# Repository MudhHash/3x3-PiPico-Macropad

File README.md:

# 9x9-PiPico-Keypad
This 9-key macropad is designed using a Raspberry Pi Pico microcontroller programmed with CircuitPython using KMK firmware.

## Overview
This repository provides the schematics and code used in this project. The goal of this project was to build a compact, low-cost, and easily programmable marcopad which ultimately serve the purpose of offering quick access to frequently used shortcuts, macros, and commands in a streamlined, tactile form.

## Bill of Materials

Item | Quantity | Cost
--- | --- | ---
Macropad PCB | 1 | $0.40 (Excluding Shipping)
Raspberry Pi Pico | 1 | $9.95 
Mechanical Keyboard Switch | 10 | $4.89
PBT Blank Keycaps | 10 | $9.59

## PCB
The PCB was designed using KiCAD with a focus on simplicity, compactness, and ease of assembly. It includes all the necessary connections for the microcontroller, switches, and diodes, while minimizing overall footprint and cost.

[Files](https://github.com/MudhHash/3x3-PiPico-Macropad/tree/main/PCB) Included:
* .kicad_pcb – Main PCB layout
* .sch – Schematic design

## Firmware and Code
This macropad uses KMK Firmware, keyboard firmware written in CircuitPython. KMK is ideal for small custom keyboards and macropads due to its ease of use, real-time reprogrammability, and active development community.

How to Implement:
* Flash the CircuitPython .uf2 file for your board from [circuitpython.org](https://circuitpython.org/downloads)
* Drag-and-drop the firmware onto the mounted USB drive (CIRCUITPY)
* Install [KMK](https://github.com/KMKfw/kmk_firmware) by copying its files into the lib directory on the device
* Add or edit the code.py file to define your keymap and macros
* Example Code:
```bash
import board  # Access pin definitions specific to the microcontroller
from kmk.kmk_keyboard import KMKKeyboard  # Base KMK keyboard class
from kmk.keys import KC  # Keycode library for standard key constants
from kmk.scanners.digitalio import DiodeOrientation  # Diode orientation options for the matrix

# Create a keyboard object instance
keyboard = KMKKeyboard()

# Define the row and column GPIO pins based on your physical wiring
keyboard.row_pins = (board.GP10, board.GP11, board.GP12)  # 3 row pins
keyboard.col_pins = (board.GP6, board.GP7, board.GP8)     # 3 column pins

# Specify the diode orientation used in the matrix (important for correct scanning)
keyboard.diode_orientation = DiodeOrientation.COL2ROW

# Define the keymap layout as a flat list of keycodes (3x3 matrix in this case)
keyboard.keymap = [
    [KC.KP_1, KC.KP_2, KC.KP_3,
     KC.KP_4, KC.KP_5, KC.KP_6,
     KC.KP_7, KC.KP_8, KC.KP_9]
]

# Run the keyboard firmware loop when the script is executed
if __name__ == '__main__':
    keyboard.go()

```

Feel free to modify the code to suit your own workflow!

## Resources
* KiCad Footprints: The component footprints used in this project were sourced from [ScottoKeebs](https://github.com/joe-scotto/scottokeebs).

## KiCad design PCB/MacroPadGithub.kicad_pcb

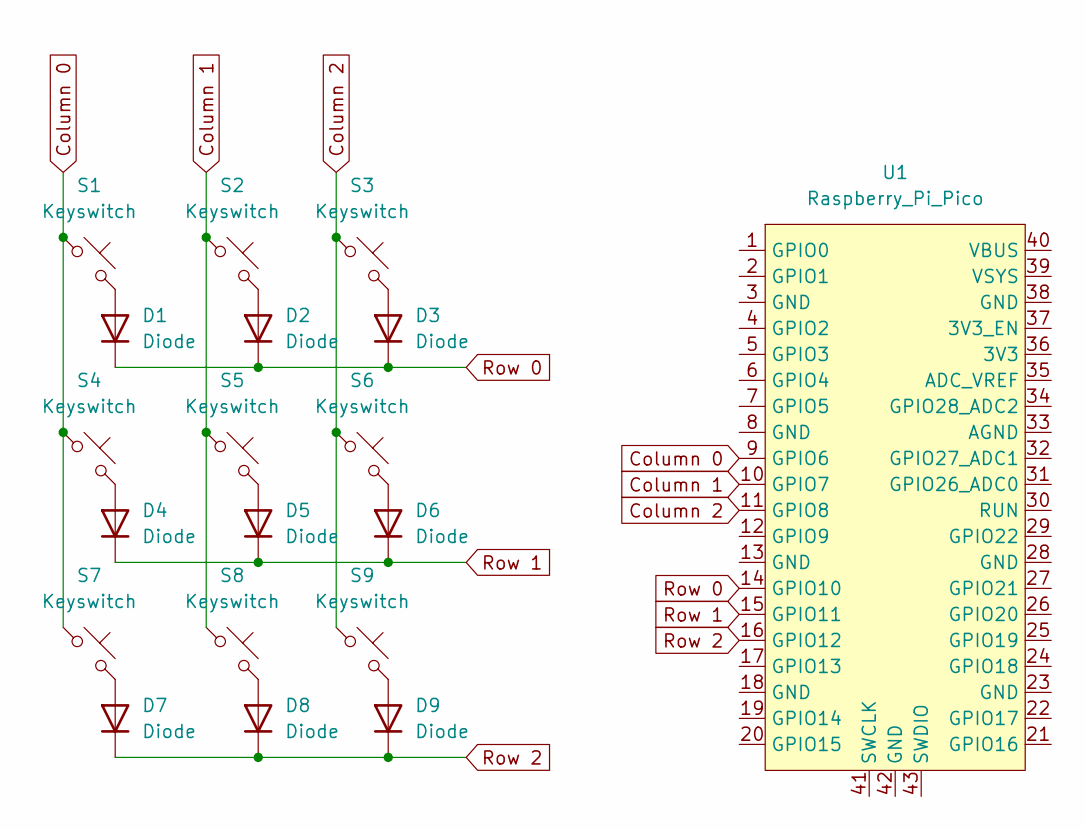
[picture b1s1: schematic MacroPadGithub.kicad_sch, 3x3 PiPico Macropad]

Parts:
D1, D2, D3, D4, D5, D6, D7, D8, D9: Diode; Diode_SOD-123
S1, S2, S3, S4, S5, S6, S7, S8, S9: Keyswitch; MX_PCB_1.00u
U1: Raspberry_Pi_Pico

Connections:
Column 0: S1.1, S4.1, S7.1, U1.9 (GPIO6)
Column 1: S2.1, S5.1, S8.1, U1.10 (GPIO7)
Column 2: S3.1, S6.1, S9.1, U1.11 (GPIO8)
unnamed: D1.2 (A), S1.2
unnamed: D2.2 (A), S2.2
unnamed: D3.2 (A), S3.2
unnamed: D4.2 (A), S4.2
unnamed: D5.2 (A), S5.2
unnamed: D6.2 (A), S6.2
unnamed: D7.2 (A), S7.2
unnamed: D8.2 (A), S8.2
unnamed: D9.2 (A), S9.2
Row 0: D1.1 (K), D2.1 (K), D3.1 (K), U1.14 (GPIO10)
Row 1: D4.1 (K), D5.1 (K), D6.1 (K), U1.15 (GPIO11)
Row 2: D7.1 (K), D8.1 (K), D9.1 (K), U1.16 (GPIO12)

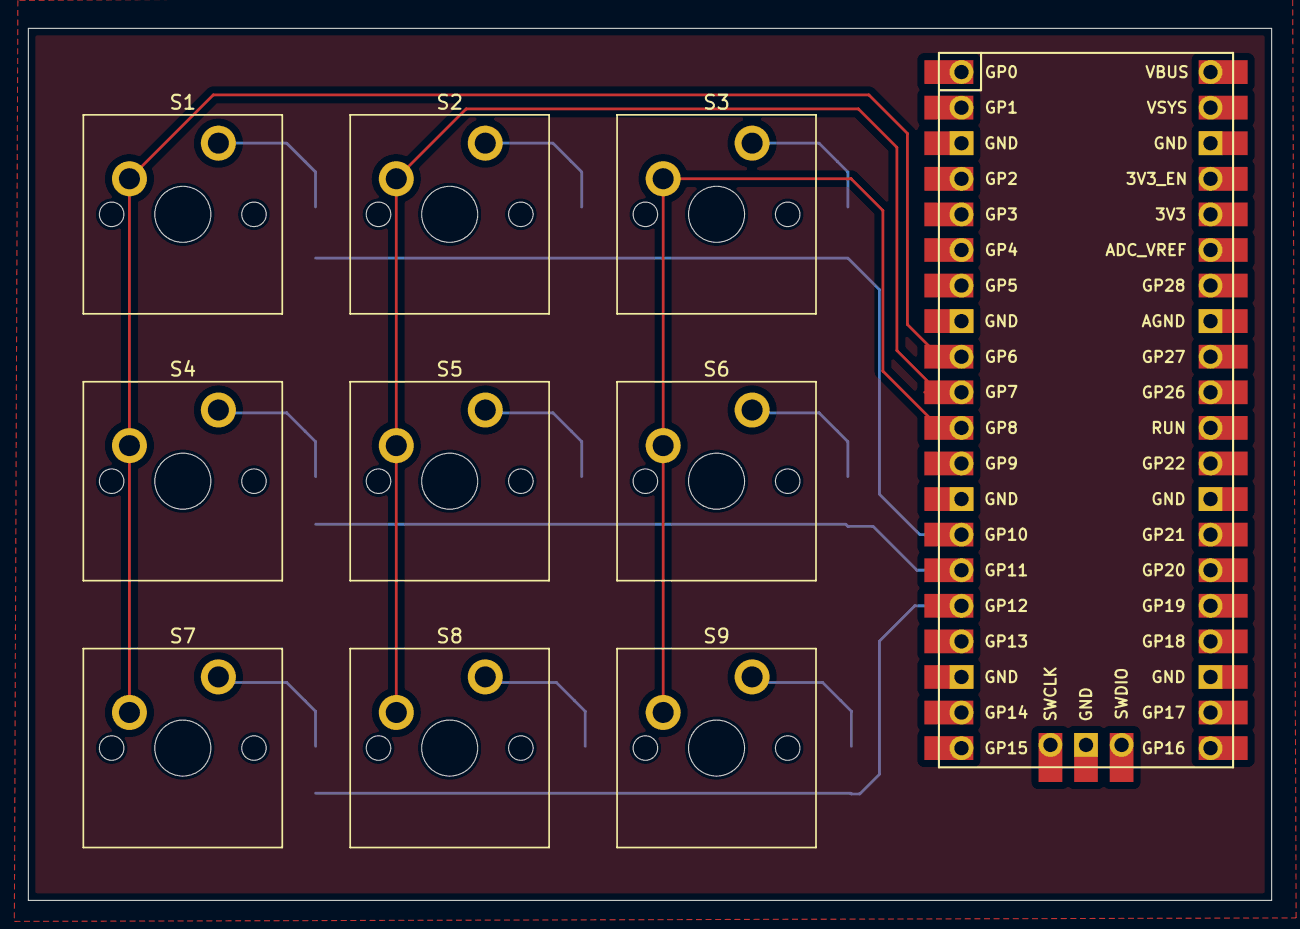
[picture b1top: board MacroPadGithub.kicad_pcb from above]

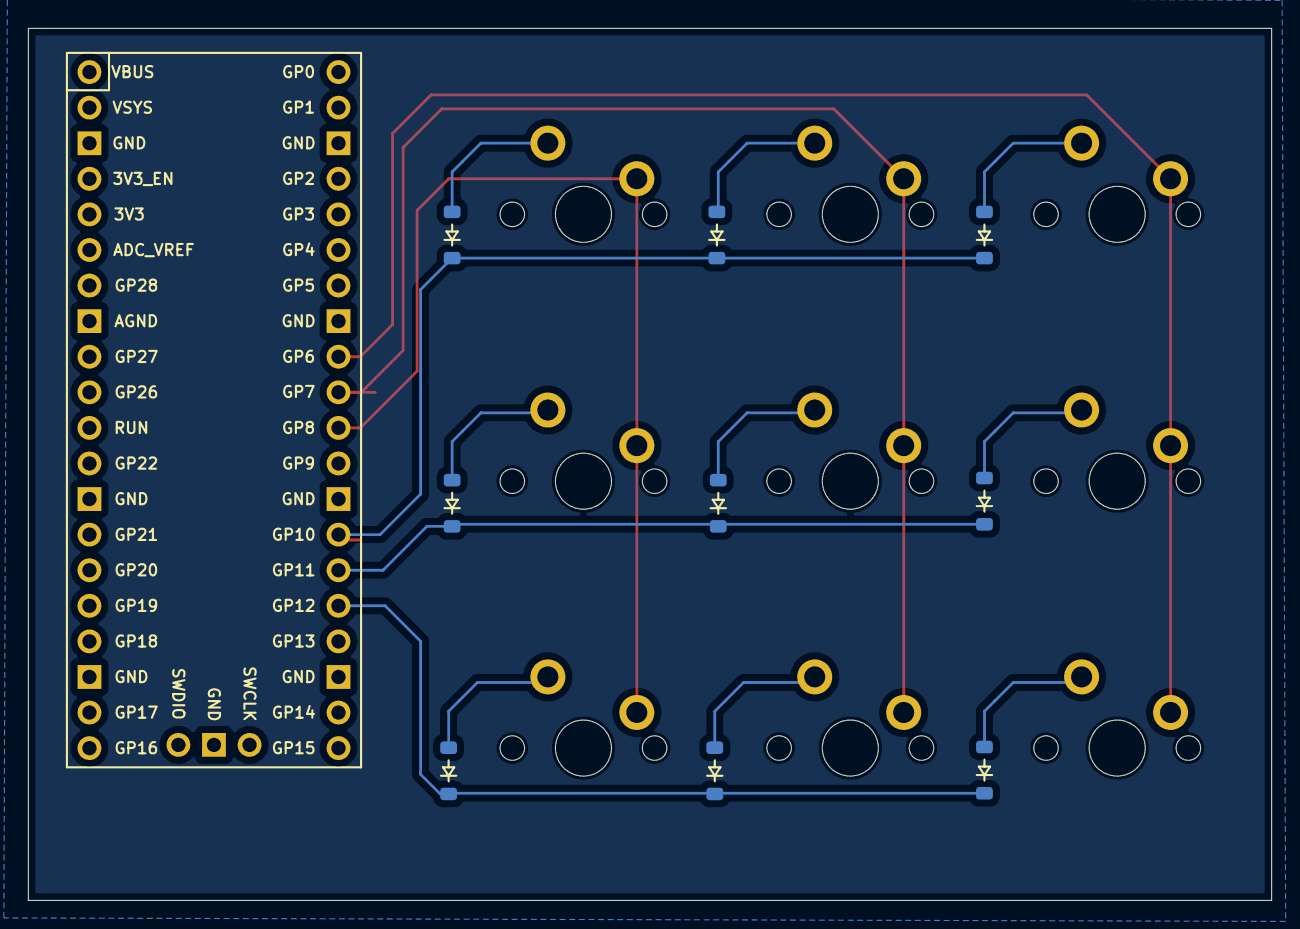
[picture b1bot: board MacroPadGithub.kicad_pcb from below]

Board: 2 copper layers, 88.7 x 62.2 mm, 20 parts (9 on the bottom side), 15 nets.

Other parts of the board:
LOGO: LOGO

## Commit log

2025-05-10 README.md
